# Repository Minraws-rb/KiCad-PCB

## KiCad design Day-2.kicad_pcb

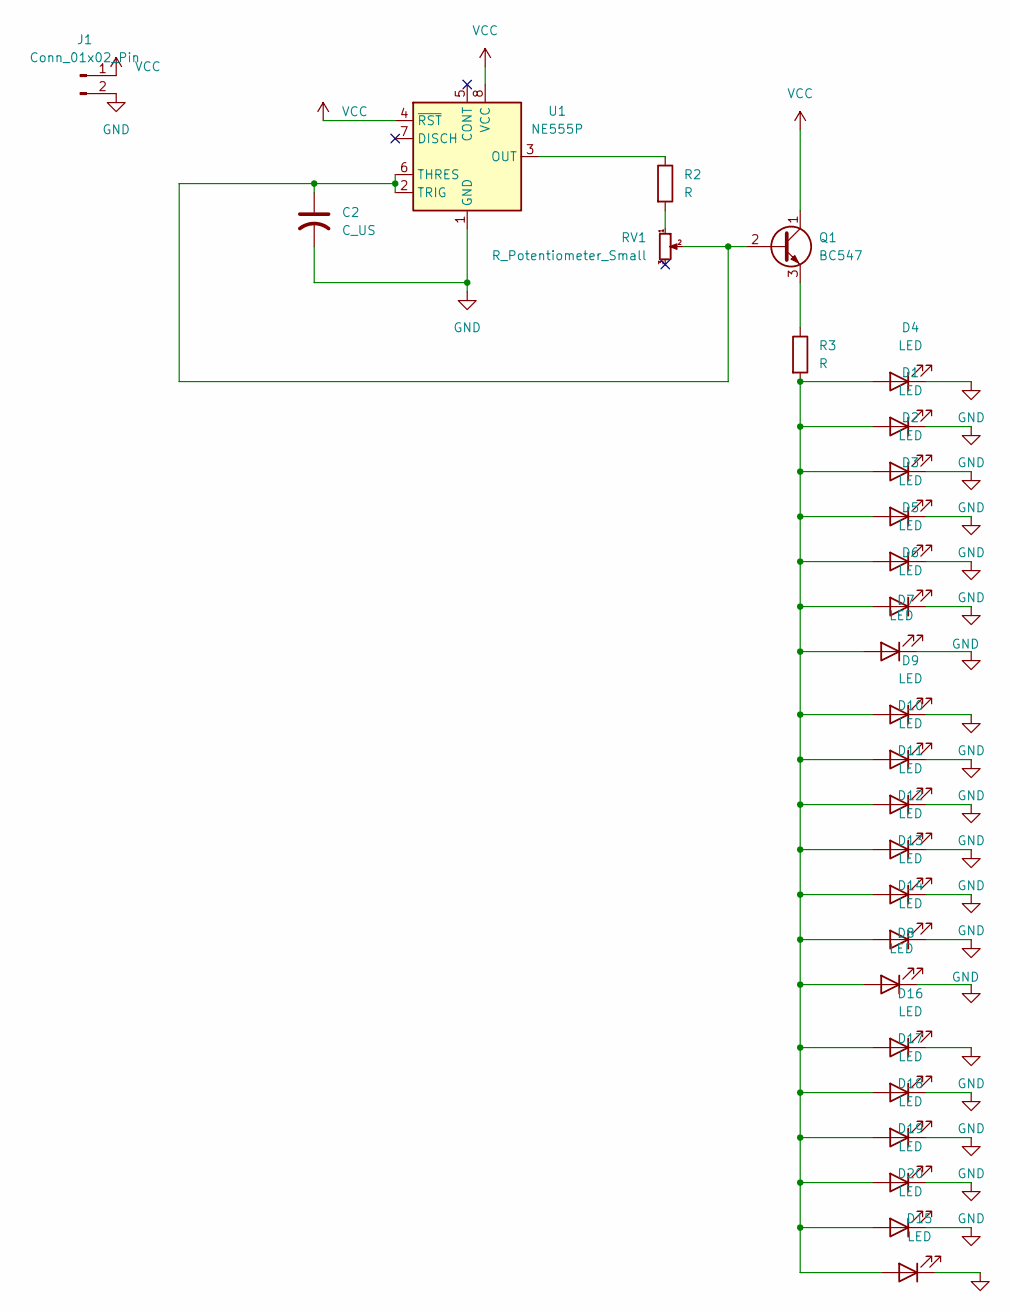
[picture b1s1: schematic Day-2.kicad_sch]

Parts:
C2: C_US; C_Radial_D6.3mm_H5.0mm_P2.50mm
D1, D2, D3, D4, D5, D6, D7, D8, D9, D10, D11, D12, D13, D14, D15, D16, D17, D18, D19, D20: LED; LED_D4.0mm
J1: Conn_01x02_Pin; PinHeader_1x02_P2.54mm_Vertical
Q1: BC547; TO-92_Inline
R2, R3: R; R_Axial_DIN0204_L3.6mm_D1.6mm_P7.62mm_Horizontal
RV1: R_Potentiometer_Small; Potentiometer_Piher_PT-10-V05_Vertical
U1: NE555P; DIP-8_W7.62mm

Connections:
GND: C2.2, D1.1 (K), D2.1 (K), D3.1 (K), D4.1 (K), D5.1 (K), D6.1 (K), D7.1 (K), D8.1 (K), D9.1 (K), D10.1 (K), D11.1 (K), D12.1 (K), D13.1 (K), D14.1 (K), D15.1 (K), D16.1 (K), D17.1 (K), D18.1 (K), D19.1 (K), D20.1 (K), J1.2, U1.1 (GND)
unnamed: D1.2 (A), D2.2 (A), D3.2 (A), D4.2 (A), D5.2 (A), D6.2 (A), D7.2 (A), D8.2 (A), D9.2 (A), D10.2 (A), D11.2 (A), D12.2 (A), D13.2 (A), D14.2 (A), D15.2 (A), D16.2 (A), D17.2 (A), D18.2 (A), D19.2 (A), D20.2 (A), R3.2
unnamed: C2.1, Q1.2 (B), RV1.2, U1.2 (TRIG), U1.6 (THRES)
unnamed: Q1.3 (E), R3.1
unnamed: R2.2, RV1.1
unnamed: R2.1, U1.3 (OUT)
VCC: J1.1, Q1.1 (C), U1.4 (~RST), U1.8 (VCC)

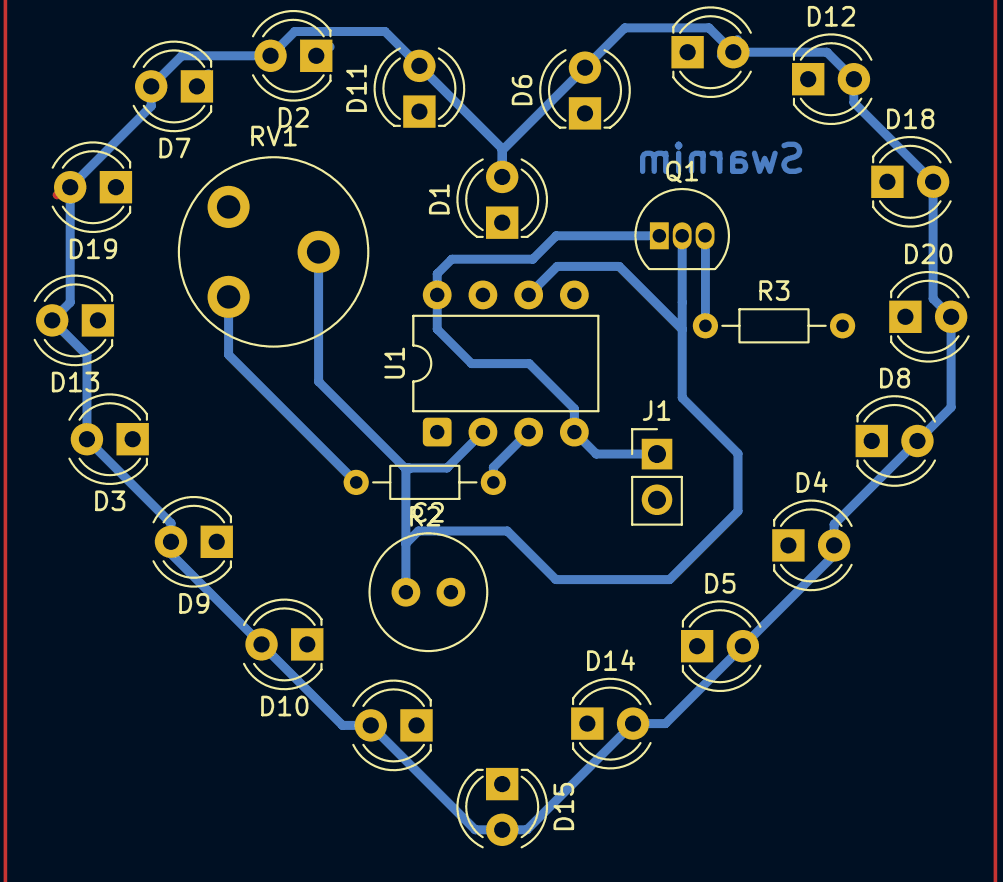
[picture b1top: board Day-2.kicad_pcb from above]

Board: 2 copper layers, 27 parts (0 on the bottom side), 7 nets.

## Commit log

2026-02-03 Add files via upload
    I made a pcb for LEDs aligning in heartshape and used 555 timer ic to make it blink in astable state.
2026-02-21 Add updated PCB documentation
2026-02-21 Rename Updated PCB to New Version/dummy
2026-02-21 Add files via upload
    This version has better routing and solved the problems of the previous version.
